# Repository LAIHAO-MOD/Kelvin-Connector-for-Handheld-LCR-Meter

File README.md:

# Kelvin-Connector-for-Handheld-LCR-Meter

Kelvin Connector for Handheld LCR Meter.

Use right angle sma connector or solder wire directly to the pcb.

recommended pcb thickness 1.0 ~ 1.2 Millimeter.

highly recommended use gold plated pcb.

assemble with  m3 screw & nuts.

Production Gerber files included.

3d printable case files included.

Use  KICAD 5.1 as Schematic & Pcb design software .

layout

3d rendering

sla 3dprinted case 

pcb

assembled

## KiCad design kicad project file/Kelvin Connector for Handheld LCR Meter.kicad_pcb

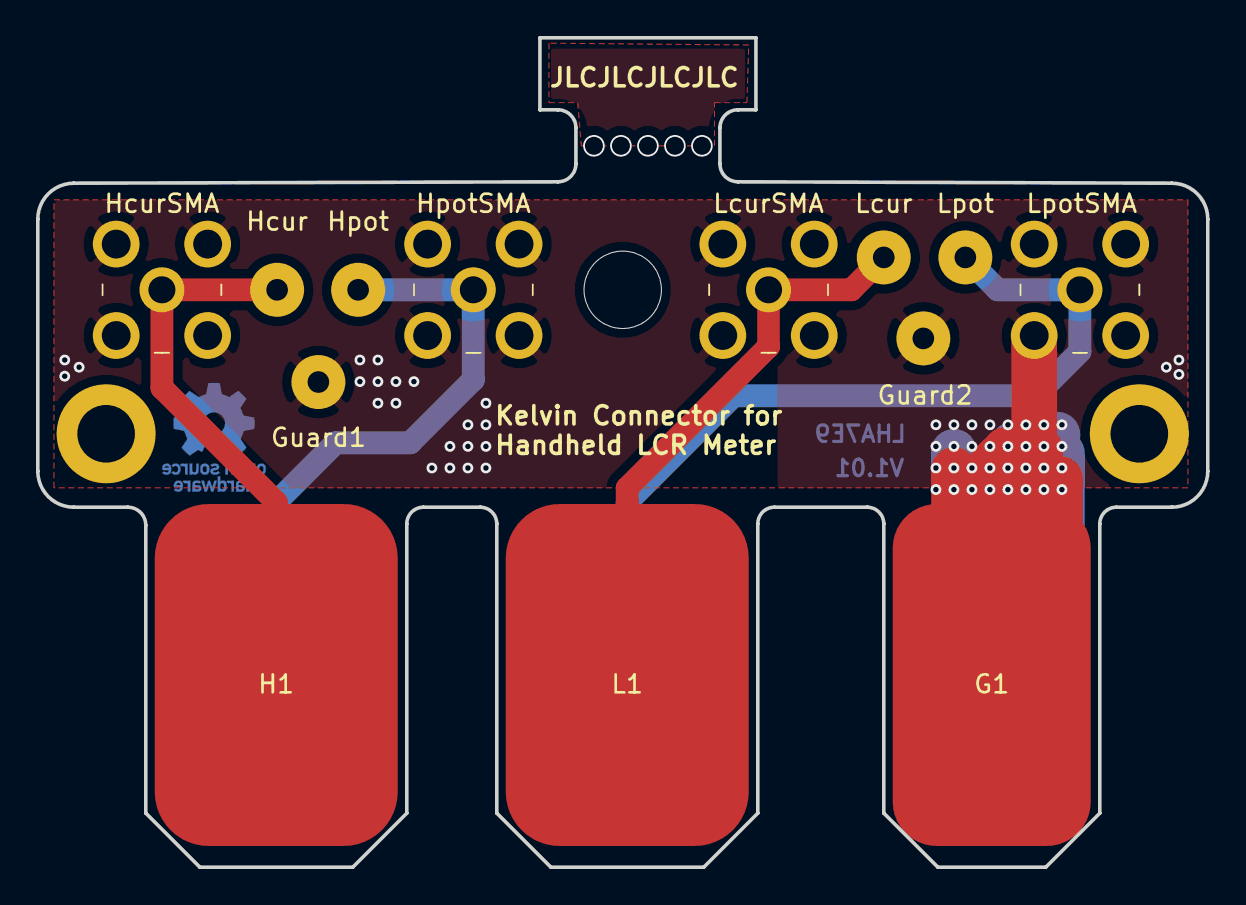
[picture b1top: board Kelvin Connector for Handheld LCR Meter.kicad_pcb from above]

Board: 2 copper layers, 65.0 x 46.1 mm, 16 parts (0 on the bottom side), 5 nets.

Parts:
G1: Conn_01x02_Male; PCB Edge connector 12-20
Guard1, Guard2: TestPoint; SolderWirePad_1x01_Drill1.2mm
H1: Conn_01x02_Male; pcb edge connector 14.5 single side
Hcur: TestPoint; SolderWirePad_1x01_Drill1.2mm
HcurSMA: 5-1814400-1; RF_SMA_RightAngle_5-1814400-1
Hpot: TestPoint; SolderWirePad_1x01_Drill1.2mm
HpotSMA: 5-1814400-1; RF_SMA_RightAngle_5-1814400-1
L1: Conn_01x02_Male; pcb edge connector 14.5 single side
Lcur: TestPoint; SolderWirePad_1x01_Drill1.2mm
LcurSMA: 5-1814400-1; RF_SMA_RightAngle_5-1814400-1
Lpot: TestPoint; SolderWirePad_1x01_Drill1.2mm
LpotSMA: 5-1814400-1; RF_SMA_RightAngle_5-1814400-1
mh1, mh2: MountingHole_3.2mm_M3_ISO14580_Pad
mh3: MountingHole_4.3mm_M4_ISO14580

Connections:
Hcur: H1.1, Hcur.1, HcurSMA.1
Hpot: H1.2, Hpot.1, HpotSMA.1
Lcur: L1.1, Lcur.1, LcurSMA.1
Lpot: L1.2, Lpot.1, LpotSMA.1
guard: G1.1, G1.2, Guard1.1, Guard2.1, HcurSMA.2, HpotSMA.2, LcurSMA.2, LpotSMA.2

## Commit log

2019-12-31 Create 1
